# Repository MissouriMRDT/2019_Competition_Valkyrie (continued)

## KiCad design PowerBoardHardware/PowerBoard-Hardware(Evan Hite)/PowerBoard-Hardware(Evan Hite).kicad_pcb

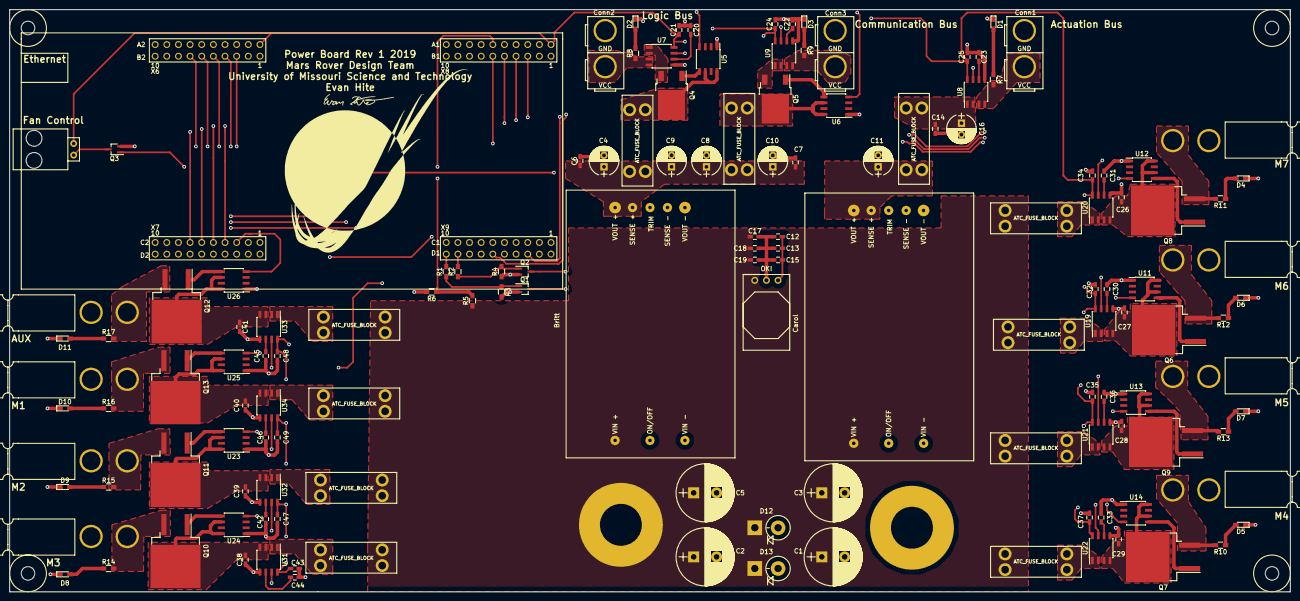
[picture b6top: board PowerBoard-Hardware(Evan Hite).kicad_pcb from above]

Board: 4 copper layers, 279.4 x 127.0 mm, 142 parts (0 on the bottom side), 99 nets.

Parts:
3V3FAN1: Molex_SL_02; MOLEX_SL_02_Horizontal
Britt: DC-DC_Converter; DC-DC_Converter_Quarter_Brick
C1, C2, C3, C5: 1m; CP_Radial_D12.5mm_P5.00mm
C4, C7, C14: 2.2u; C_0603_HandSoldering
C6, C8, C9, C10, C11, C16: 330u; CP_Radial_D6.3mm_P2.50mm
C12, C17, C20, C22, C23, C30, C31, C33, C36, C42, C44, C45, C46: 1n; C_0603_HandSoldering
C13, C18: 10u; C_0603_HandSoldering
C15, C19, C21, C24, C25, C27, C28, C29, C32, C34, C35, C37, C38, C39, C40, C41, C43, C47, C48, C49: 0.1u; C_0603_HandSoldering
C26: 0.1; C_0603_HandSoldering
Carol: DC-DC_Converter; DC-DC_Converter_Quarter_Brick
Conn1, Conn2, Conn3: AndersonPP; Vertical Anderson Double
Conn4, Conn5, Conn6, Conn7, Conn8, Conn9, Conn10, Conn11: AndersonPP; Anderson_2_Vertical
D1, D2, D3, D4, D5, D6, D7, D8, D9, D10, D11: LED; LED_0603_HandSoldering
D12, D13: 1.5KE36; D_DO-201AD_P5.08mm_Vertical_KathodeUp
GND: GND; BATT_PWR_VIA
PVDD: PVDD; BATT_PWR_VIA
Q1, Q2, Q3: IPT020N10N3; SOT-323_SC-70_Handsoldering
Q4, Q5: IPT020N10N3; TO-252-2
Q6, Q7, Q8, Q9, Q10, Q11, Q12, Q13: Q_NMOS_GDS; TO-263-2
R1, R2, R7, R8, R9: 1k; R_0603_HandSoldering
R3, R4, R5: 100k; R_0603_HandSoldering
R6: 10k; R_0603_HandSoldering
R10, R11, R12, R13, R14, R15, R16, R17: 5k; R_0603_HandSoldering
U1: TM4C129E_Launchpad; TM4C129E_Launchpad_FULL
U2, U3, U4, U15, U16, U17, U18, U27, U28, U29, U30: ATC_FUSE_BLOCK; ATC_Fuse_Block
U5, U6, U11, U12, U13, U14, U23, U24, U25, U26: LT1910; SOIC-8_3.9x4.9mm_Pitch1.27mm
U7, U8, U9, U19, U20, U21, U22, U31, U32, U33, U34: ACS714xLCTR-05B; SOIC-8_3.9x4.9mm_Pitch1.27mm
U10: OKI; OKI_Horizontal

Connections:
3.3V: 3V3FAN1.2, C12.1, C13.1, C15.1, C21.2, C24.2, C25.2, C32.2, C34.2, C35.2, C37.2, C43.2, C47.2, C48.2, C49.2, U1.+3V3, U7.8, U8.8, U9.8, U10.3, U19.8, U20.8, U21.8, U22.8, U31.8, U32.8, U33.8, U34.8
ACT-CTL: R2.2, U1.PN3
COM-SIG: U1.PD1, U6.4
FAN-CTL: Q3.1, U1.PM3
GND: Britt.3, Britt.4, Britt.5, C1.2, C2.2, C3.2, C4.2, C5.2, C6.2, C7.1, C8.2, C9.2, C10.2, C11.2, C12.2, C13.2, C14.2, C15.2, C16.2, C17.2, C18.2, C19.2, C20.2, C21.1, C22.2, C23.2, C24.1, C25.1, C26.2, C27.2, C28.2, C29.2, C30.1, C31.1, C32.1, C33.1, C34.1, C35.1, C36.1, C37.1, C38.2, C39.2, C40.2, C41.2, C42.1, C43.1, C44.1, C45.1, C46.1, C47.1, C48.1, C49.1, Carol.3, Carol.4, Carol.5, Conn1.1, Conn2.1, Conn3.1, Conn4.1, Conn5.1, Conn6.1, Conn7.1, Conn8.1, Conn9.1, Conn10.1, Conn11.1, D1.1, D2.1, D3.1, D4.1, D5.1, D6.1, D7.1, D8.1, D9.1, D10.1, D11.1, D12.2, D13.2, GND.1, Q1.2, Q2.2, Q3.2, R3.2, R4.1, R6.2, U1.GND, U5.1, U6.1, U7.5, U8.5, U9.5, U10.2, U11.1, U12.1, U13.1, U14.1, U19.5, U20.5, U21.5, U22.5, U23.1, U24.1, U25.1, U26.1, U31.5, U32.5, U33.5, U34.5
IMEAS-ACT: U1.PE2, U8.7
IMEAS-AUX: U1.PD0, U33.7
IMEAS-COM: U1.PE1, U9.7
IMEAS-LOGIC: U1.PE0, U7.7
IMEAS-M1: U1.PK3, U34.7
IMEAS-M2: U1.PK2, U32.7
IMEAS-M3: U1.PK1, U31.7
IMEAS-M4: U1.PK0, U22.7
IMEAS-M5: U1.PB5, U21.7
IMEAS-M6: U1.PB4, U19.7
IMEAS-M7: U1.PE3, U20.7
LOGIC-SIG: U1.PH2, U5.4
LOGIC\COM-CTL: R1.2, U1.PP2
unnamed: 3V3FAN1.1, Q3.3
unnamed: Britt.7, Britt.8, C4.1, C6.1, C7.2, C8.1, C9.1, C10.1, U2.1, U4.1
unnamed: C11.1, Carol.7, Carol.8, U3.1
unnamed: C14.1, C16.1, U3.2, U8.1, U8.2
unnamed: C20.1, U7.6
unnamed: C22.1, U9.6
unnamed: C23.1, U8.6
unnamed: C26.1, Q8.2, U12.6, U12.8, U20.3, U20.4
unnamed: C27.1, Q6.2, U11.6, U11.8, U19.3, U19.4
unnamed: C28.1, Q9.2, U13.6, U13.8, U21.3, U21.4
unnamed: C29.1, Q7.2, U14.6, U14.8, U22.3, U22.4
unnamed: C30.2, U19.6
unnamed: C31.2, U20.6
unnamed: C33.2, U22.6
unnamed: C36.2, U21.6
unnamed: C38.1, Q10.2, U24.6, U24.8, U31.3, U31.4
unnamed: C39.1, Q11.2, U23.6, U23.8, U32.3, U32.4
unnamed: C40.1, Q13.2, U25.6, U25.8, U34.3, U34.4
unnamed: C41.1, Q12.2, U26.6, U26.8, U33.3, U33.4
unnamed: C42.2, U32.6
unnamed: C44.2, U31.6
unnamed: C45.2, U33.6
unnamed: C46.2, U34.6
unnamed: Britt.2, Q1.3
unnamed: Carol.2, Q2.3
unnamed: Conn1.2, R7.2, U8.3, U8.4
unnamed: Conn2.2, R8.2, U7.3, U7.4
unnamed: Conn3.2, R9.2, U9.3, U9.4
unnamed: Conn4.2, Q8.3, R11.2
unnamed: Conn5.2, Q6.3, R12.2
unnamed: Conn6.2, Q9.3, R13.2
unnamed: Conn7.2, Q7.3, R10.2
unnamed: Conn8.2, Q12.3, R17.2
unnamed: Conn9.2, Q13.3, R16.2
unnamed: Conn10.2, Q11.3, R15.2
unnamed: Conn11.2, Q10.3, R14.2
unnamed: D1.2, R7.1
unnamed: D2.2, R8.1
unnamed: D3.2, R9.1
unnamed: D4.2, R11.1
unnamed: D5.2, R10.1
unnamed: D6.2, R12.1
unnamed: D7.2, R13.1
unnamed: D8.2, R14.1
unnamed: D9.2, R15.1
unnamed: D10.2, R16.1
unnamed: D11.2, R17.1
unnamed: Q1.1, R1.1, R3.1
unnamed: Q2.1, R2.1, R4.2
unnamed: Q4.1, U5.5
unnamed: Q4.2, U4.2, U5.6, U5.8
unnamed: Q4.3, U7.1, U7.2
unnamed: Q5.1, U6.5
unnamed: Q5.2, U2.2, U6.6, U6.8
unnamed: Q5.3, U9.1, U9.2
unnamed: Q6.1, U11.5
unnamed: Q7.1, U14.5
unnamed: Q8.1, U12.5
unnamed: Q9.1, U13.5
unnamed: Q10.1, U24.5
unnamed: Q11.1, U23.5
unnamed: Q12.1, U26.5
unnamed: Q13.1, U25.5
unnamed: U15.2, U19.1, U19.2
unnamed: U16.2, U20.1, U20.2
unnamed: U17.2, U21.1, U21.2
unnamed: U18.2, U22.1, U22.2
unnamed: U27.2, U31.1, U31.2
unnamed: U28.2, U34.1, U34.2
unnamed: U29.2, U32.1, U32.2
unnamed: U30.2, U33.1, U33.2
PVDD: Britt.1, C1.1, C2.1, C3.1, C5.1, C17.1, C18.1, C19.1, Carol.1, D12.1, D13.1, PVDD.1, R5.1, U10.1, U15.1, U16.1, U17.1, U18.1, U27.1, U28.1, U29.1, U30.1
SIG-AUX: U1.PK5, U26.4
SIG-M1: U1.PK7, U25.4
SIG-M2: U1.PK6, U23.4
SIG-M3: U1.PH1, U24.4
SIG-M4: U1.PH0, U14.4
SIG-M5: U1.PM2, U13.4
SIG-M6: U1.PM1, U11.4
SIG-M7: U1.PM0, U12.4
VMEAS-VBATT: R5.2, R6.1, U1.PE5
